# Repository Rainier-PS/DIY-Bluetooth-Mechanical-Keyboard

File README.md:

# DIY Bluetooth Mechanical Keyboard

## 1. Description

The DIY Bluetooth Mechanical Keyboard is a custom-designed 3D printed wireless keyboard with an ergonomic 6 degree tilt, a slide potentiometer for analog input, USB Type-C connectivity, and hot-swappable MX-style switches. It includes a detachable wrist rest for comfort and features embedded passive NFC tags that can be used for mobile automations or other creative integrations.  

This keyboard was made to be easily built and remixed by others. The entire design uses mostly through-hole components. Only the diodes are surface-mount, which makes it much easier to assemble without needing any special tools.

---

## 2. Why I Made This Project

I designed this keyboard for myself with daily use in mind. I wanted something compact, reliable, and comfortable to use, especially during long sessions. Most wireless keyboards don't come with embedded passive NFC tags and some still even use micro USB for charging and wired mode. This one uses USB Type-C and Bluetooth, and can also be recharged easily.

The project also gave me a chance to learn about PCB layout, 3D CAD, component sourcing, and firmware setup. I wanted to build something I could be proud of and share with others who might want to build their own.

---

## Project Gallery

---

### 3D CAD Model  

---

### PCB Design  

---

### Wiring Diagram  

---

## Bill of Materials (BOM)

| No. | Category            | Item                   | Qty    | Est. Price (USD) | Description / Notes                                     | Link |
|-----|---------------------|------------------------|--------|------------------|---------------------------------------------------------|------|
| 1   | Switch & Keycap     | Gateron Milky Yellow Pro | 64 pcs | 12               | Smooth linear switches with factory lube                | https://www.tokopedia.com/mechkeyboardsid/gateron-g-pro-yellow-switch-linear-plate-mount?utm_source=salinlink&utm_medium=share&utm_campaign=PDP-266238606-2999811194-130725-RKdhUE |
| 2   | Switch & Keycap     | Kailh Hot Swap Sockets | 64 pcs | 5                | For hot-swappable MX-style switches                     | https://www.tokopedia.com/mechkeyboardsid/kailh-hot-swap-mechanical-keyboard-pcb-socket-black?utm_source=salinlink&utm_medium=share&utm_campaign=PDP-266238606-2198706891-130725-RKdhUE |
| 3   | Switch & Keycap     | Keycap Set             | 1 set  | 20               | Full keycap set, likely PBT                             | https://tk.tokopedia.com/ZSBVvFJGR/ |
| 4   | Switch & Keycap     | Stabilizer Set         | 1 set  | 10               | For spacebar, shift, enter, etc.                        | https://tk.tokopedia.com/ZSBpk1MKy/ |
| 5   | Electronics         | Nice!Nano V2 (Clone)   | 2 pcs  | 8                | Wireless controller with ZMK support                    | https://tk.tokopedia.com/ZSSLQ4ugF/ |
| 6   | Electronics         | MCP23017 E/SP          | 1 pc   | 7                | GPIO Expander                                           | https://www.tokopedia.com/iibuuffeellaaa/ic-chips-mcp23017-e-sp-dip-28-mcp23017-16-bit-i-o-expander-with-i2c-interface-ic-original-integrated-circuits-1731233355557078588?utm_source=salinlink&utm_medium=share&utm_campaign=PDP-266238606-100273252298-270725-RKdhUE |
| 7   | Electronics         | LiPo Battery           | 1 pc   | 4                | Powers the keyboard wirelessly                          | https://tk.tokopedia.com/ZSBpAFa1Y/ |
| 8   | Electronics         | JST Connector          | 1 pc   | 1                | Connects battery to PCB                                 | https://tk.tokopedia.com/ZSBpAYkm3/ |
| 9   | Electronics         | 1N4148 Diodes (SOD-123) | 100 pcs | 1               | For keyboard matrix                                     | https://www.tokopedia.com/i2c-parts/in4148-1n4148-1n4148ws-sod123-switching-diode-sod-123-dioda?utm_source=salinlink&utm_medium=share&utm_campaign=PDP-266238606-1509220482-130725-RKdhUE |
| 10  | Electronics         | 10K Slide Potentiometers | 10 pcs | 1               | For analog controls like volume                         | https://www.tokopedia.com/innovtronic/b10k-mono-slide-potentio-75mm-high-quality?utm_source=salinlink&utm_medium=share&utm_campaign=PDP-266238606-344656821-130725-RKdhUE |
| 11  | Fasteners           | M2.5 6mm Heat Inserts  | 6 pcs  | 1                | For securing threaded parts in plastic                  | https://tk.tokopedia.com/ZSBqKcnqk/ |
| 12  | Fasteners           | M2.5 8mm Screws        | 6 pcs  | 1                | For case and PCB mounting                               | https://www.tokopedia.com/archive-lapaktukang/baut-komputer-laptop-m2-5x4-m2-5x5-m2-5x6-m2-5x8-m2-5x10-m2-5x8-mm-hitam-d5-7f72b?utm_source=salinlink&utm_medium=share&utm_campaign=PDP-266238606-14063028572-140725-RKdhUE |
| 13  | Damping & Isolation | EVA Foam 3mm           | 1 pc   | 2                | For internal case dampening                             | https://www.tokopedia.com/tentakey/eva-foam-untuk-case-plate-foam-modding-mechanical-keyboard-25x30-2mm-26c32?utm_source=salinlink&utm_medium=share&utm_campaign=PDP-266238606-8737440897-140725-RKdhUE |
| 14  | Damping & Isolation | Non-slip Feet          | 1 set  | 1                | Anti-slip support                                       | https://tk.tokopedia.com/ZSBqsCjBn/ |
| 15  | Assembly            | Solder Wire            | 1 pc   | 2                | For assembling components                               | https://tk.tokopedia.com/ZSAR33vra/ |
| 16  | Assembly            | Solder Paste           | 1 pc   | 3                | For assembling components (SMD)                         | https://tk.tokopedia.com/ZSAR3KArf/ |
| 17  | Assembly            | Flux                   | 1 pc   | 1                | Improves solder quality, especially for SMD components  | |
| 18  | PCB & Electronics   | Custom PCB             | 5 pcs  | 16               | Custom-designed keyboard circuit board                  | — |
| 19  | Case Components     | Case                   | 1 pc   | 3                | One-piece keyboard case (price is reserved for shipping, tentative) | — |
| 20  | Case Components     | Wristrest              | 1 pc   | 3                | Wristrest (price is reserved for shipping, tentative)   | — |
| 21  | Feature Add-on      | Passive NFC Tags       | 1 pack | 4                | Embedded for automation (e.g. launch phone shortcut)    | https://tk.tokopedia.com/ZSBVtqGWa/ |

Total: $106 USD

> Prices are rounded up to the next whole dollar.

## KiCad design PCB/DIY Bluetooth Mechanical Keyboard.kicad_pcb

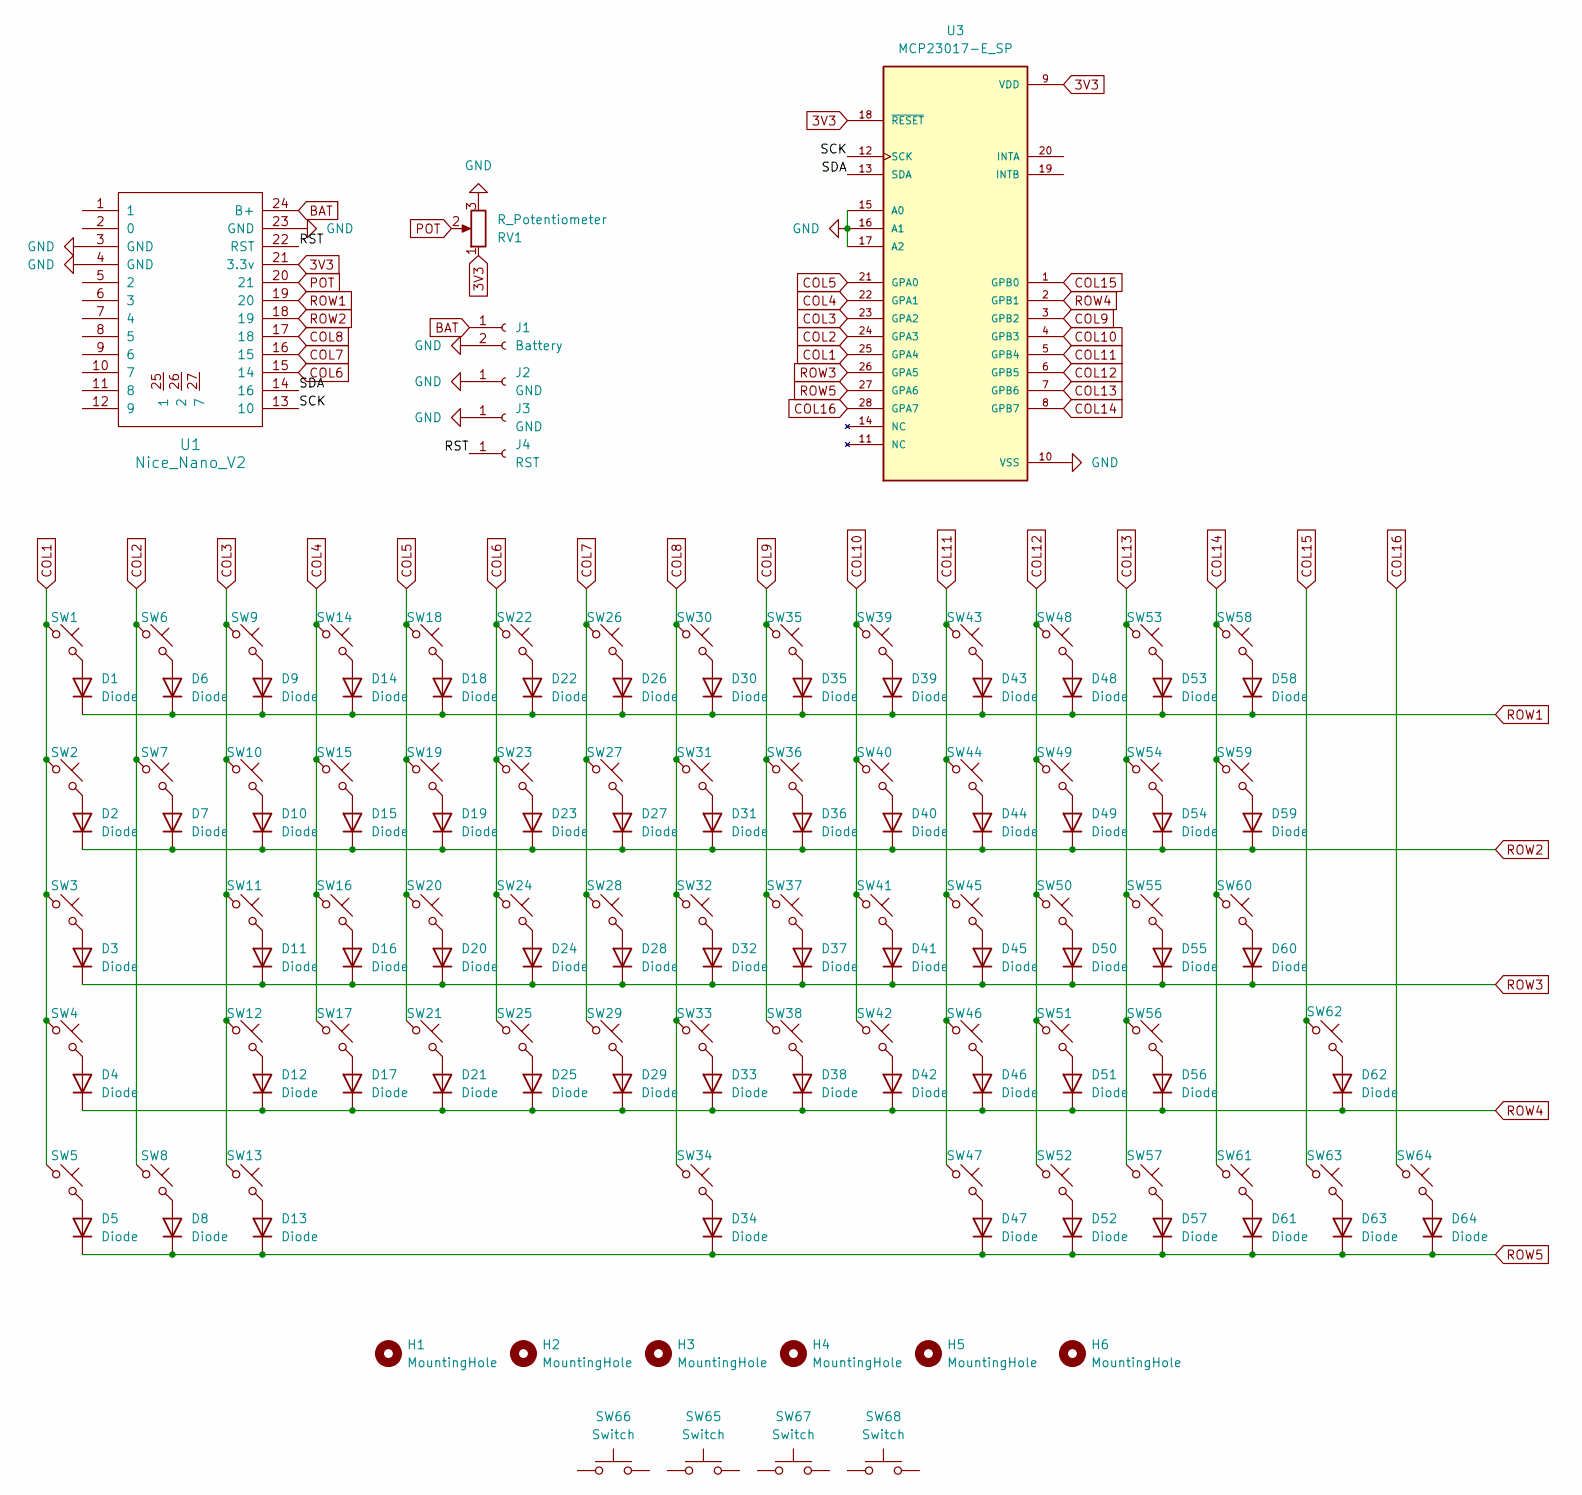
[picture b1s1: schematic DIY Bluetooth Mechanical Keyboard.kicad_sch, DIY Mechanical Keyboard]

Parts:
D1, D2, D3, D4, D5, D6, D7, D8, D9, D10, D11, D12, D13, D14, D15, D16, D17, D18, D19, D20, D21, D22, D23, D24, D25, D26, D27, D28, D29, D30, D31, D32, D33, D34, D35, D36, D37, D38, D39, D40, D41, D42, D43, D44, D45, D46, D47, D48, D49, D50, D51, D52, D53, D54, D55, D56, D57, D58, D59, D60, D61, D62, D63, D64: Diode; D_0805_2012Metric_Pad1.15x1.40mm_HandSolder
H1, H2, H3, H4, H5, H6: MountingHole; MountingHole_2.7mm_M2.5
J1: Battery; JST_PH_B2B-PH-K_1x02_P2.00mm_Vertical
J2: GND; TestPoint_THTPad_D2.0mm_Drill1.0mm
J3: GND; TestPoint_Pad_1.5x1.5mm
J4: RST; TestPoint_Pad_1.5x1.5mm
RV1: R_Potentiometer; Sliding_Pot
SW1, SW6, SW7, SW8, SW9, SW10, SW11, SW12, SW13, SW14, SW15, SW16, SW17, SW18, SW19, SW20, SW21, SW22, SW23, SW24, SW25, SW26, SW27, SW28, SW29, SW30, SW31, SW32, SW33, SW35, SW36, SW37, SW38, SW39, SW40, SW41, SW42, SW43, SW44, SW45, SW46, SW48, SW49, SW50, SW51, SW53, SW54, SW55, SW57, SW61, SW62, SW63, SW64: SW_Push_45deg; Hotswap_MX_Plated_1.00u
SW2, SW59: SW_Push_45deg; Hotswap_MX_Plated_1.50u
SW3, SW56: SW_Push_45deg; Hotswap_MX_Plated_1.75u
SW4, SW60: SW_Push_45deg; Hotswap_MX_Plated_2.25u
SW5, SW47, SW52: SW_Push_45deg; Hotswap_MX_Plated_1.25u
SW34: SW_Push_45deg; Hotswap_MX_Plated_6.25u
SW58: SW_Push_45deg; Hotswap_MX_Plated_2.00u
SW65, SW66, SW67: Switch; Stabilizer_MX_2.00u
SW68: Switch; Stabilizer_MX_6.25u
U1: Nice_Nano_V2
U3: MCP23017-E_SP; DIP787W45P254L3556H508Q28; PARTREV D

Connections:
3V3: RV1.1, U1.21 (3.3v), U3.9 (VDD), U3.18 (~RESET)
/RST: J4.1, U1.22 (RST); also elsewhere on the board
/SCK: U1.13 (10), U3.12 (SCK)
/SDA: U1.14 (16), U3.13 (SDA)
BAT: J1.1, U1.24 (B+); also elsewhere on the board
COL1: SW1.1, SW2.1, SW3.1, SW4.1, SW5.1, U3.25 (GPA4)
COL2: SW6.1, SW7.1, SW8.1, U3.24 (GPA3)
COL3: SW9.1, SW10.1, SW11.1, SW12.1, SW13.1, U3.23 (GPA2)
COL4: SW14.1, SW15.1, SW16.1, SW17.1, U3.22 (GPA1)
COL5: SW18.1, SW19.1, SW20.1, SW21.1, U3.21 (GPA0)
COL6: SW22.1, SW23.1, SW24.1, SW25.1, U1.15 (14)
COL7: SW26.1, SW27.1, SW28.1, SW29.1, U1.16 (15)
COL8: SW30.1, SW31.1, SW32.1, SW33.1, SW34.1, U1.17 (18)
COL9: SW35.1, SW36.1, SW37.1, SW38.1, U3.3 (GPB2)
COL10: SW39.1, SW40.1, SW41.1, SW42.1, U3.4 (GPB3)
COL11: SW43.1, SW44.1, SW45.1, SW46.1, SW47.1, U3.5 (GPB4)
COL12: SW48.1, SW49.1, SW50.1, SW51.1, SW52.1, U3.6 (GPB5)
COL13: SW53.1, SW54.1, SW55.1, SW56.1, SW57.1, U3.7 (GPB6)
COL14: SW58.1, SW59.1, SW60.1, SW61.1, U3.8 (GPB7)
COL15: SW62.1, SW63.1, U3.1 (GPB0)
COL16: SW64.1, U3.28 (GPA7)
GND: J1.2, J2.1, J3.1, RV1.3, U1.3 (GND), U1.4 (GND), U1.23 (GND), U3.10 (VSS), U3.15 (A0), U3.16 (A1), U3.17 (A2); also elsewhere on the board
unnamed: D1.2 (A), SW1.2
unnamed: D2.2 (A), SW2.2
unnamed: D3.2 (A), SW3.2
unnamed: D4.2 (A), SW4.2
unnamed: D5.2 (A), SW5.2
unnamed: D6.2 (A), SW6.2
unnamed: D7.2 (A), SW7.2
unnamed: D8.2 (A), SW8.2
unnamed: D9.2 (A), SW9.2
unnamed: D10.2 (A), SW10.2
unnamed: D11.2 (A), SW11.2
unnamed: D12.2 (A), SW12.2
unnamed: D13.2 (A), SW13.2
unnamed: D14.2 (A), SW14.2
unnamed: D15.2 (A), SW15.2
unnamed: D16.2 (A), SW16.2
unnamed: D17.2 (A), SW17.2
unnamed: D18.2 (A), SW18.2
unnamed: D19.2 (A), SW19.2
unnamed: D20.2 (A), SW20.2
unnamed: D21.2 (A), SW21.2
unnamed: D22.2 (A), SW22.2
unnamed: D23.2 (A), SW23.2
unnamed: D24.2 (A), SW24.2
unnamed: D25.2 (A), SW25.2
unnamed: D26.2 (A), SW26.2
unnamed: D27.2 (A), SW27.2
unnamed: D28.2 (A), SW28.2
unnamed: D29.2 (A), SW29.2
unnamed: D30.2 (A), SW30.2
unnamed: D31.2 (A), SW31.2
unnamed: D32.2 (A), SW32.2
unnamed: D33.2 (A), SW33.2
unnamed: D34.2 (A), SW34.2
unnamed: D35.2 (A), SW35.2
unnamed: D36.2 (A), SW36.2
unnamed: D37.2 (A), SW37.2
unnamed: D38.2 (A), SW38.2
unnamed: D39.2 (A), SW39.2
unnamed: D40.2 (A), SW40.2
unnamed: D41.2 (A), SW41.2
unnamed: D42.2 (A), SW42.2
unnamed: D43.2 (A), SW43.2
unnamed: D44.2 (A), SW44.2
unnamed: D45.2 (A), SW45.2
unnamed: D46.2 (A), SW46.2
unnamed: D47.2 (A), SW47.2
unnamed: D48.2 (A), SW48.2
unnamed: D49.2 (A), SW49.2
unnamed: D50.2 (A), SW50.2
unnamed: D51.2 (A), SW51.2
unnamed: D52.2 (A), SW52.2
unnamed: D53.2 (A), SW53.2
unnamed: D54.2 (A), SW54.2
unnamed: D55.2 (A), SW55.2
unnamed: D56.2 (A), SW56.2
unnamed: D57.2 (A), SW57.2
unnamed: D58.2 (A), SW58.2
unnamed: D59.2 (A), SW59.2
unnamed: D60.2 (A), SW60.2
unnamed: D61.2 (A), SW61.2
unnamed: D62.2 (A), SW62.2
unnamed: D63.2 (A), SW63.2
unnamed: D64.2 (A), SW64.2
POT: RV1.2, U1.20 (21)
ROW1: D1.1 (K), D6.1 (K), D9.1 (K), D14.1 (K), D18.1 (K), D22.1 (K), D26.1 (K), D30.1 (K), D35.1 (K), D39.1 (K), D43.1 (K), D48.1 (K), D53.1 (K), D58.1 (K), U1.19 (20)
ROW2: D2.1 (K), D7.1 (K), D10.1 (K), D15.1 (K), D19.1 (K), D23.1 (K), D27.1 (K), D31.1 (K), D36.1 (K), D40.1 (K), D44.1 (K), D49.1 (K), D54.1 (K), D59.1 (K), U1.18 (19)
ROW3: D3.1 (K), D11.1 (K), D16.1 (K), D20.1 (K), D24.1 (K), D28.1 (K), D32.1 (K), D37.1 (K), D41.1 (K), D45.1 (K), D50.1 (K), D55.1 (K), D60.1 (K), U3.26 (GPA5)
ROW4: D4.1 (K), D12.1 (K), D17.1 (K), D21.1 (K), D25.1 (K), D29.1 (K), D33.1 (K), D38.1 (K), D42.1 (K), D46.1 (K), D51.1 (K), D56.1 (K), D62.1 (K), U3.2 (GPB1)
ROW5: D5.1 (K), D8.1 (K), D13.1 (K), D34.1 (K), D47.1 (K), D52.1 (K), D57.1 (K), D61.1 (K), D63.1 (K), D64.1 (K), U3.27 (GPA6)

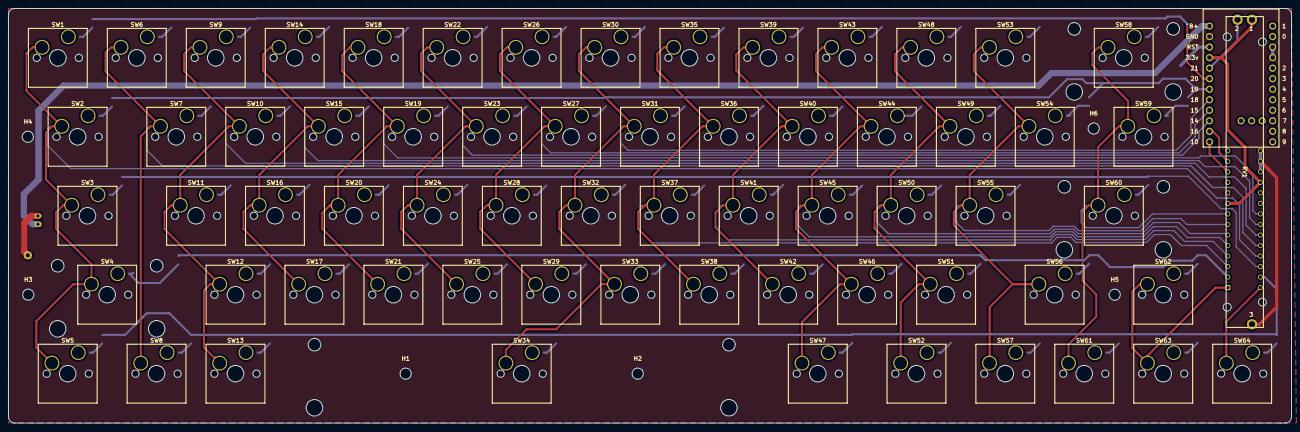
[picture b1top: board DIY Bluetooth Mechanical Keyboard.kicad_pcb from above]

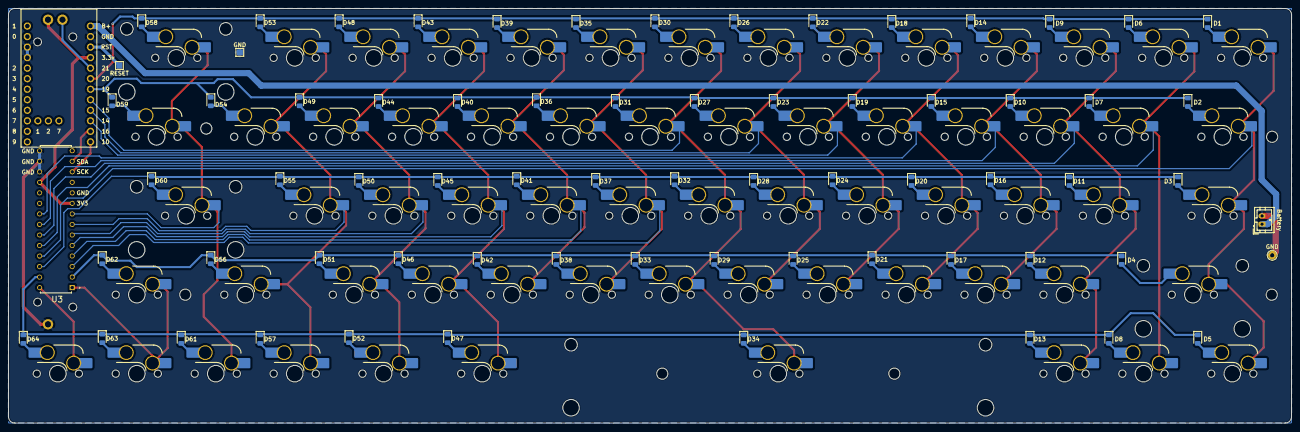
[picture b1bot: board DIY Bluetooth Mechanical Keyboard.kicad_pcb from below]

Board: 2 copper layers, 309.6 x 100.0 mm, 145 parts (70 on the bottom side), 92 nets.

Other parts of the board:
Battery: Battery; JST_PH_B2B-PH-K_1x02_P2.00mm_Vertical
GND: GND; TestPoint_THTPad_D2.0mm_Drill1.0mm
GND#2: GND; TestPoint_Pad_1.5x1.5mm
RESET: RST; TestPoint_Pad_1.5x1.5mm

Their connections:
/RST: RESET.1; also elsewhere on the board
BAT: Battery.1; also elsewhere on the board
GND: Battery.2, GND.1, GND#2.1; also elsewhere on the board

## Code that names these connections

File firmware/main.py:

from kmk.kmk_keyboard import KMKKeyboard
from kmk.modules.layers import Layers
from kmk.scanners.keypad import MatrixScanner
from kmk.scanners.analog import AnalogScanner
from kmk.keys import KC

import board
import busio
from adafruit_mcp230xx.mcp23017 import MCP23017

keyboard = KMKKeyboard()
keyboard.modules.append(Layers())

# --- Setup I2C and MCP23017 ---
i2c = busio.I2C(scl=board.D10, sda=board.D16)  # GPIO10=SCL, GPIO16=SDA
mcp = MCP23017(i2c, address=0x20)  # A0, A1, A2 grounded -> 0x20

# --- MCP23017 Pins ---
mcp_rows = [
    mcp.get_pin(5),   # GPA5 = ROW3
    mcp.get_pin(1 + 8),  # GPB1 = ROW4
    mcp.get_pin(6),   # GPA6 = ROW5
]

mcp_cols = [
    mcp.get_pin(4),   # GPA4 = COL1
    mcp.get_pin(3),   # GPA3 = COL2
    mcp.get_pin(2),   # GPA2 = COL3
    mcp.get_pin(1),   # GPA1 = COL4
    mcp.get_pin(0),   # GPA0 = COL5
    mcp.get_pin(2 + 8),   # GPB2 = COL9
    mcp.get_pin(3 + 8),   # GPB3 = COL10
    mcp.get_pin(4 + 8),   # GPB4 = COL11
    mcp.get_pin(5 + 8),   # GPB5 = COL12
    mcp.get_pin(6 + 8),   # GPB6 = COL13
    mcp.get_pin(7 + 8),   # GPB7 = COL14
    mcp.get_pin(0 + 8),   # GPB0 = COL15
    mcp.get_pin(7),   # GPA7 = COL16
]

# Set direction for MCP pins
for pin in mcp_rows:
    pin.switch_to_input(pull=None)
for pin in mcp_cols:
    pin.switch_to_output(value=True)

# --- Nice!Nano Direct Pins ---
direct_rows = [
    board.D20,  # GPIO20 = ROW1
    board.D19,  # GPIO19 = ROW2
]

direct_cols = [
    board.D14,  # GPIO14 = COL6
    board.D15,  # GPIO15 = COL7
    board.D18,  # GPIO18 = COL8
]

# --- Combine into a single matrix ---
# Order: COL1–COL16, ROW1–ROW5

keyboard.matrix = MatrixScanner(
    cols=mcp_cols + direct_cols,  # COL1–COL16 (MCP) + COL6–COL8 (Direct)
    rows=direct_rows + mcp_rows,  # ROW1–ROW5 (2 Direct + 3 MCP)
    columns_to_anodes=True
)

# --- KEYMAP (Example Only!) ---
keyboard.keymap = [
    [  # row x column layout: 5 rows × 16 columns
        KC.ESC, KC._1, KC._2, KC._3, KC._4, KC._5, KC._6, KC._7, KC._8, KC._9, KC._0, KC.MINS, KC.EQL, KC.BSPC, KC.NO, KC.NO,
        KC.TAB, KC.Q, KC.W, KC.E, KC.R, KC.T, KC.Y, KC.U, KC.I, KC.O, KC.P, KC.LBRC, KC.RBRC, KC.BSLS, KC.NO, KC.NO,
        KC.CAPS, KC.A, KC.S, KC.D, KC.F, KC.G, KC.H, KC.J, KC.K, KC.L, KC.SCLN, KC.QUOT, KC.NO, KC.ENT, KC.NO, KC.NO,
        KC.LSFT, KC.Z, KC.X, KC.C, KC.V, KC.B, KC.N, KC.M, KC.COMM, KC.DOT, KC.SLSH, KC.NO, KC.NO, KC.NO, KC.NO, KC.RSFT,
        KC.LCTL, KC.LGUI, KC.LALT, KC.SPC, KC.SPC, KC.RALT, KC.RGUI, KC.APP, KC.LEFT, KC.DOWN, KC.UP, KC.RGHT, KC.NO, KC.NO, KC.NO, KC.RCTL,
    ]
]

if __name__ == '__main__':
    keyboard.go()

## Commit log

2025-07-14 Create temp
2025-07-15 Rename July 14 2025_Final.png to July 15 2025_Final.png
2025-07-15 Rename July 13 2025_Switch.png to July 14 2025_Switch.png
2025-07-15 Rename July 12 2025_Case.png to July 13 2025_Case.png
2025-07-31 Rename PCB-Gerbers.zip to production/PCB-Gerbers.zip
